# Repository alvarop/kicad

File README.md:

These are some of my KiCAD projects.

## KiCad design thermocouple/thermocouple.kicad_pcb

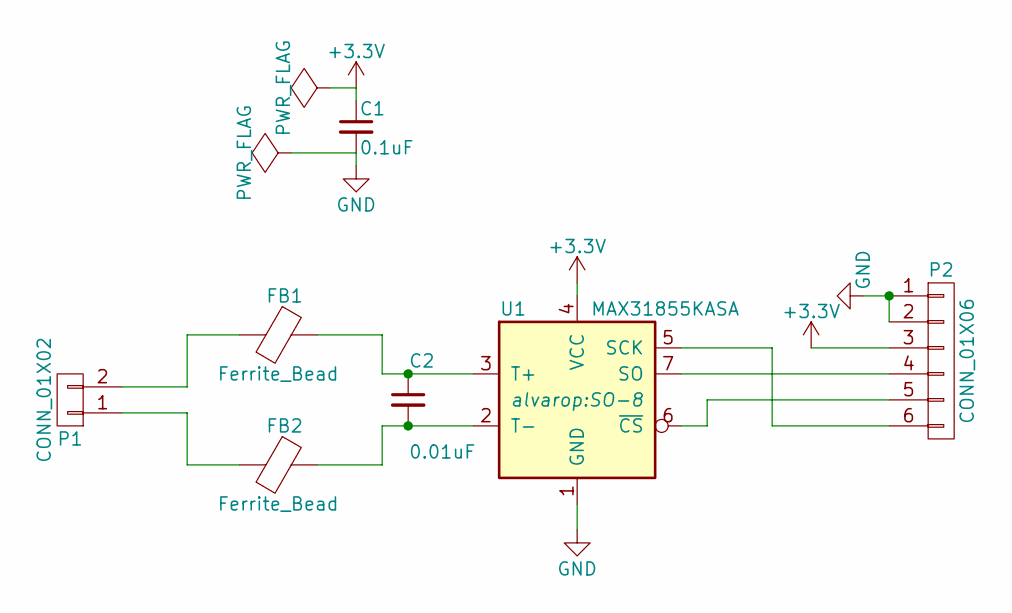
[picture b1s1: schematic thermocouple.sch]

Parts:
C1: 0.1uF; C_0805; MPN CL21B104MBCNNNC
C2: 0.01uF; C_0805; MPN CL21B103KBANNNC
FB1, FB2: Ferrite_Bead; R_0603; MPN BLM18PG471SN1D
P1: CONN_01X02; Pin_Header_Straight_1x02_Pitch2.54mm
P2: CONN_01X06; Pin_Header_Straight_1x06_Pitch2.54mm
U1: MAX31855KASA; SO-8; MPN MAX31855KASA+

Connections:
+3V3: C1.1, P2.3, U1.4 (VCC)
GND: C1.2, P2.1, P2.2, U1.1 (GND)
unnamed: C2.1, FB1.1, U1.3 (T+)
unnamed: C2.2, FB2.1, U1.2 (T-)
unnamed: FB1.2, P1.2
unnamed: FB2.2, P1.1
unnamed: P2.4, U1.7 (SO)
unnamed: P2.5, U1.6 (~CS~)
unnamed: P2.6, U1.5 (SCK)

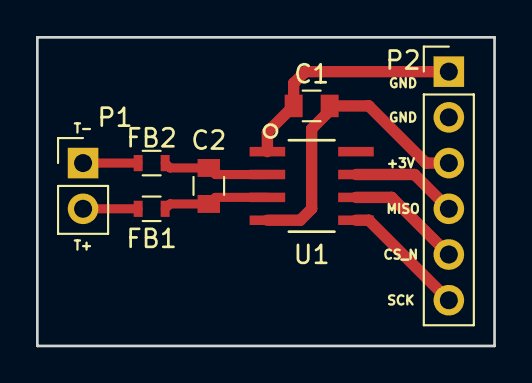
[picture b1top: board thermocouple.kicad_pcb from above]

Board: 2 copper layers, 25.4 x 17.1 mm, 7 parts (0 on the bottom side), 9 nets.

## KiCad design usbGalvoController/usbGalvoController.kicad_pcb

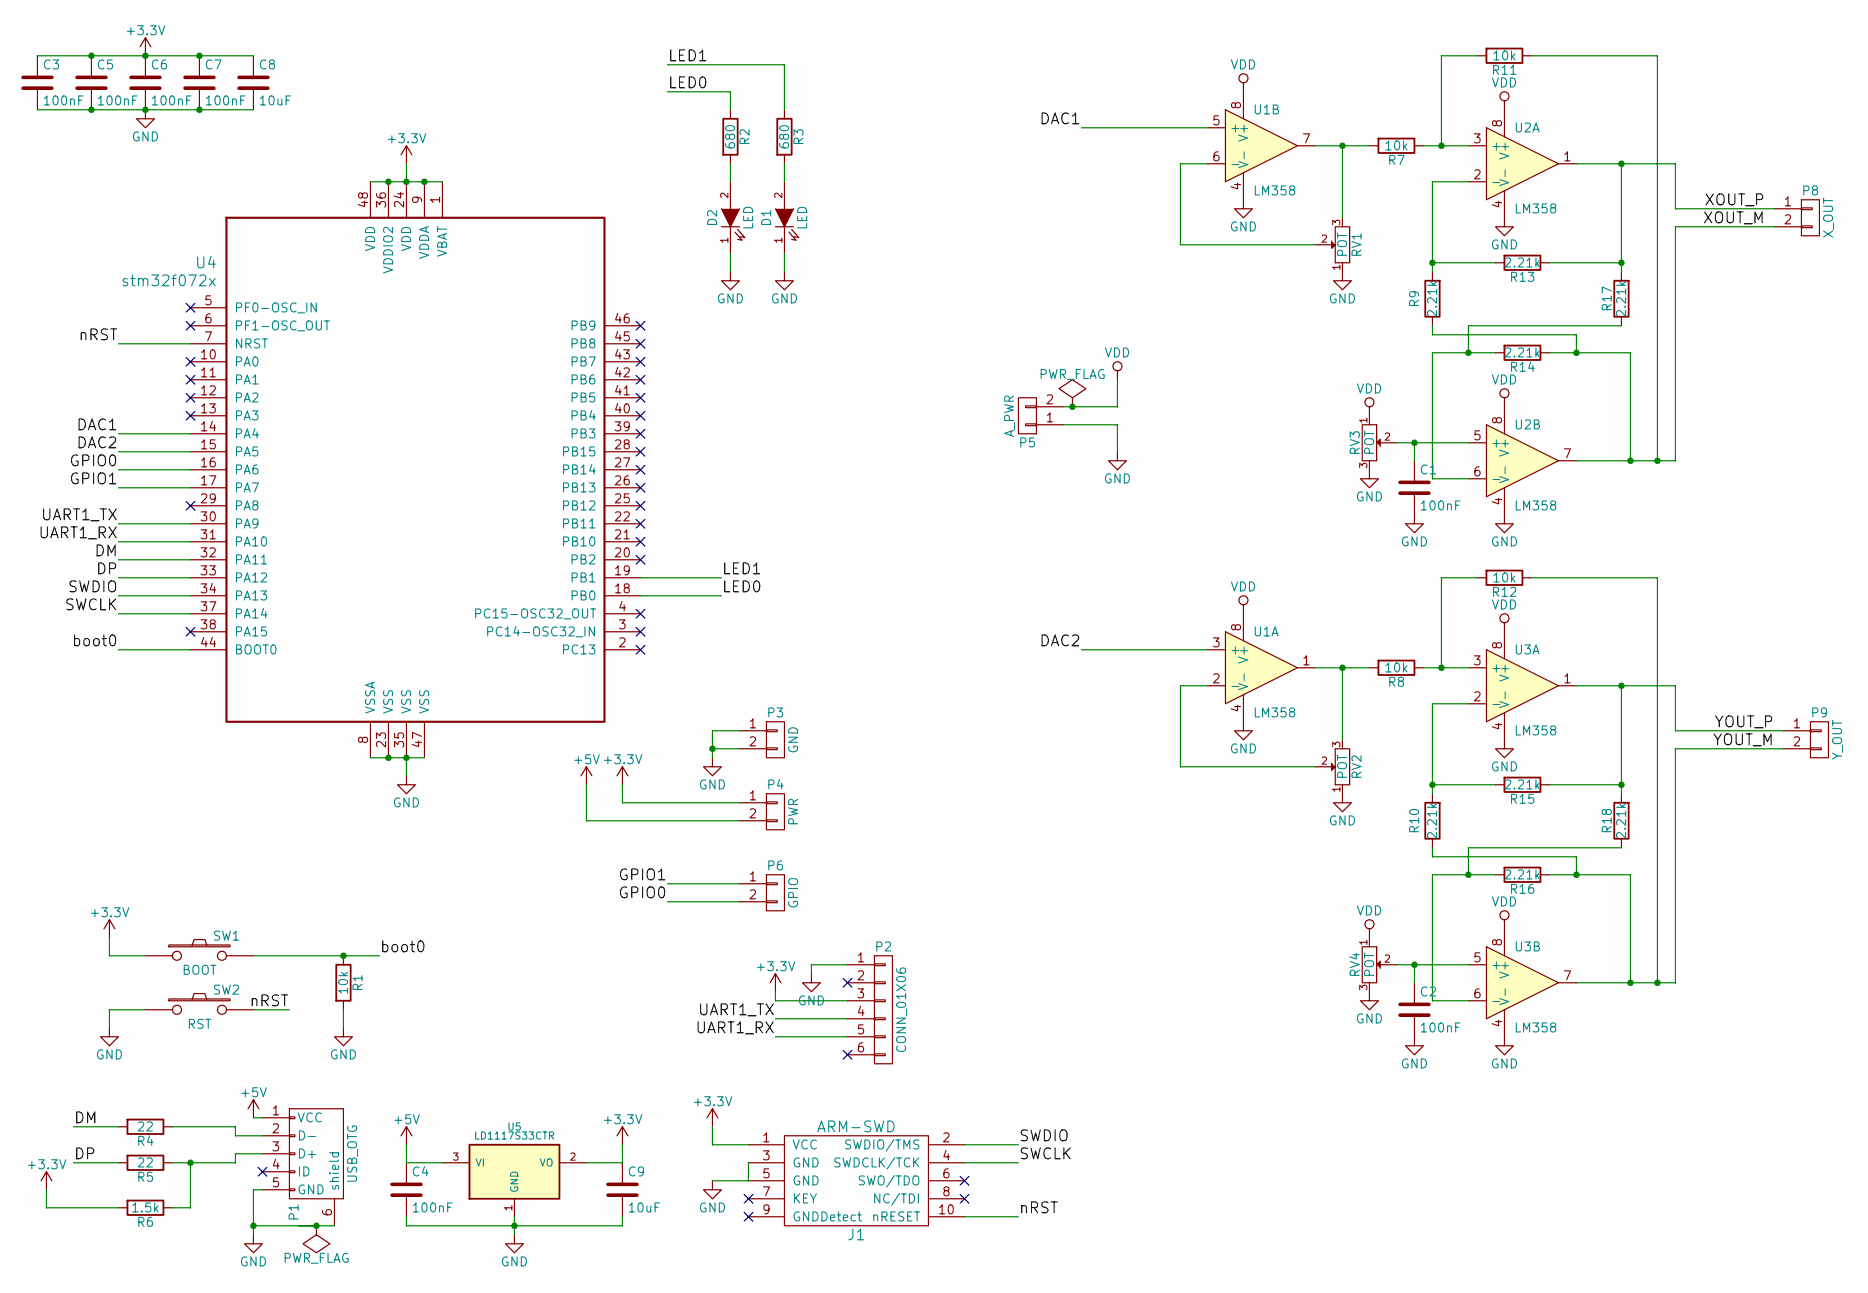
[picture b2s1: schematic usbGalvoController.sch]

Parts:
C1, C2, C3, C4, C5, C6, C7: 100nF; C_0805
C8, C9: 10uF; C_0805
D1, D2: LED; LED_0805
J1: ARM-SWD; ARM_SWD_SMD
P1: USB_OTG; USB_MICRO_B
P2: CONN_01X06; Pin_Header_Straight_1x06
P3: GND; Pin_Header_Straight_1x02
P4: PWR; Pin_Header_Straight_1x02
P5: A_PWR; Pin_Header_Straight_1x02
P6: GPIO; Pin_Header_Straight_1x02
P8: X_OUT; Pin_Header_Straight_1x02
P9: Y_OUT; Pin_Header_Straight_1x02
R1, R7, R8, R11, R12: 10k; R_0805
R2, R3: 680; R_0805
R4, R5: 22; R_0805
R6: 1.5k; R_0805
R9, R10, R13, R14, R15, R16, R17, R18: 2.21k; R_0805
RV1, RV2, RV3, RV4: POT; POT-4mm
SW1: BOOT; PTS645SM43SMTR92
SW2: RST; PTS645SM43SMTR92
U1, U2, U3: LM358; SOIC-8_3.9x4.9mm_Pitch1.27mm
U4: stm32f072x; LQFP48
U5: LD1117S33CTR; SOT-223

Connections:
+3V3: C3.1, C5.1, C6.1, C7.1, C8.1, C9.1, J1.1 (VCC), P2.3, P4.1, R6.2, SW1.1, U4.1 (VBAT), U4.9 (VDDA), U4.24 (VDD), U4.36 (VDDIO2), U4.48 (VDD), U5.2 (VO)
+5V: C4.1, P1.1 (VCC), P4.2, U5.3 (VI)
/DAC1: U1.5 (+), U4.14 (PA4)
/DAC2: U1.3 (+), U4.15 (PA5)
/DM: R4.2, U4.32 (PA11)
/DP: R5.2, U4.33 (PA12)
/GPIO0: P6.2, U4.16 (PA6)
/GPIO1: P6.1, U4.17 (PA7)
/LED0: R2.1, U4.18 (PB0)
/LED1: R3.1, U4.19 (PB1)
/SWCLK: J1.4 (SWDCLK/TCK), U4.37 (PA14)
/SWDIO: J1.2 (SWDIO/TMS), U4.34 (PA13)
/UART1_RX: P2.5, U4.31 (PA10)
/UART1_TX: P2.4, U4.30 (PA9)
/XOUT_M: P8.2, R9.1, R11.1, R14.1, U2.7
/XOUT_P: P8.1, R13.1, R17.2, U2.1
/YOUT_M: P9.2, R10.1, R12.1, R16.1, U3.7
/YOUT_P: P9.1, R15.1, R18.2, U3.1
/boot0: R1.1, SW1.2, U4.44 (BOOT0)
/nRST: J1.10 (nRESET), SW2.2, U4.7 (NRST)
GND: C1.2, C2.2, C3.2, C4.2, C5.2, C6.2, C7.2, C8.2, C9.2, D1.1 (K), D2.1 (K), J1.3 (GND), J1.5 (GND), P1.5 (GND), P1.6 (shield), P2.1, P3.1, P3.2, P5.1, R1.2, RV1.1, RV2.1, RV3.3, RV4.3, SW2.1, U1.4 (V-), U2.4 (V-), U3.4 (V-), U4.8 (VSSA), U4.23 (VSS), U4.35 (VSS), U4.47 (VSS), U5.1 (GND)
unnamed: C1.1, RV3.2, U2.5 (+)
unnamed: C2.1, RV4.2, U3.5 (+)
unnamed: D1.2 (A), R3.2
unnamed: D2.2 (A), R2.2
unnamed: P1.2 (D-), R4.1
unnamed: P1.3 (D+), R5.1, R6.1
unnamed: R7.2, RV1.3, U1.7
unnamed: R8.2, RV2.3, U1.1
unnamed: R10.2, R15.2, U3.2 (-)
unnamed: R7.1, R11.2, U2.3 (+)
unnamed: R8.1, R12.2, U3.3 (+)
unnamed: R9.2, R13.2, U2.2 (-)
unnamed: R14.2, R17.1, U2.6 (-)
unnamed: R16.2, R18.1, U3.6 (-)
unnamed: RV1.2, U1.6 (-)
unnamed: RV2.2, U1.2 (-)
VDD: P5.2, RV3.1, RV4.1, U1.8 (V+), U2.8 (V+), U3.8 (V+)

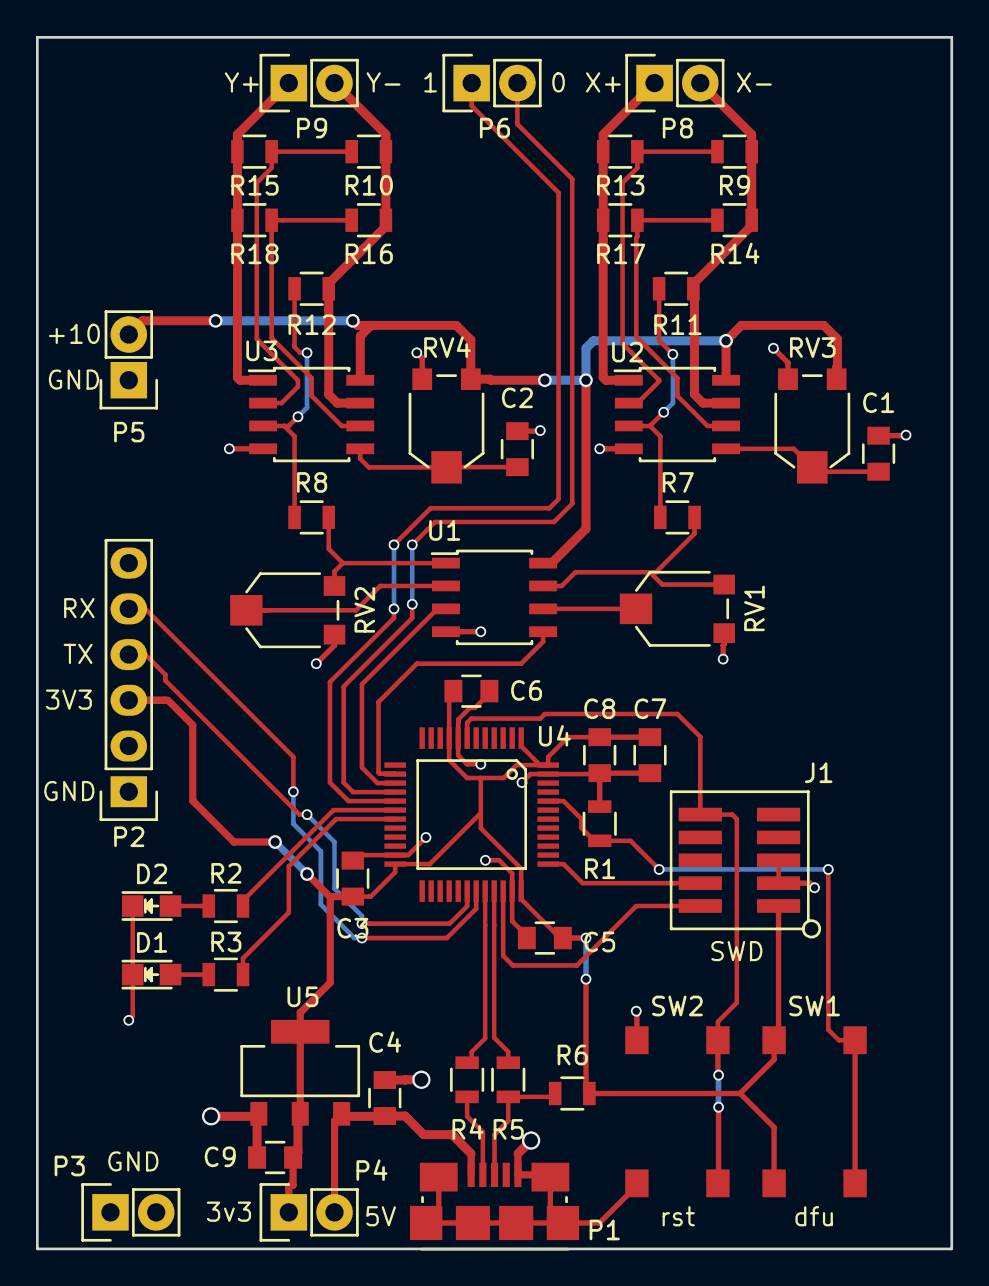
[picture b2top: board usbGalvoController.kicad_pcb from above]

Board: 2 copper layers, 50.8 x 67.3 mm, 49 parts (0 on the bottom side), 38 nets.

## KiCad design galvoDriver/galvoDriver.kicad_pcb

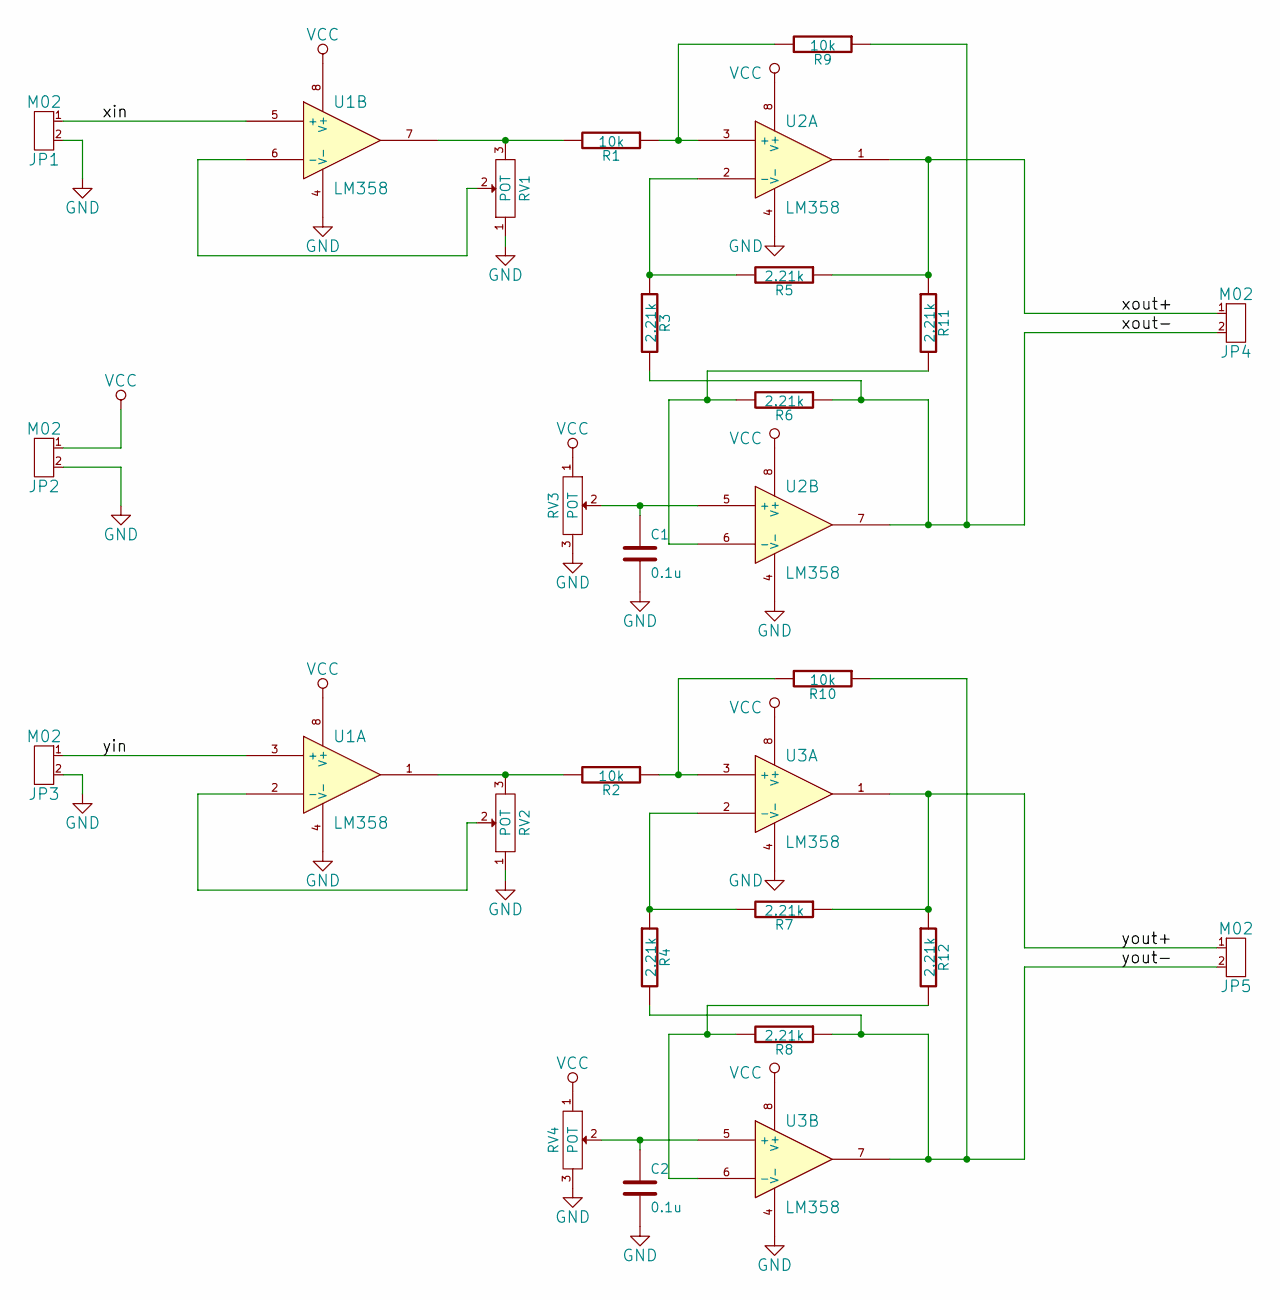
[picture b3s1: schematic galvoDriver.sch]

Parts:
C1, C2: 0.1u; C_0805
JP1, JP2, JP3, JP4, JP5: M02; Pin_Header_Straight_1x02
R1, R2, R9, R10: 10k; R_0805
R3, R4, R5, R6, R7, R8, R11, R12: 2.21k; R_0805
RV1, RV2, RV3, RV4: POT; POT-4mm
U1, U2, U3: LM358; SOIC-8_3.9x4.9mm_Pitch1.27mm

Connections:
/xin: JP1.1, U1.5 (+)
/xout+: JP4.1, R5.1, R11.1, U2.1
/xout-: JP4.2, R3.2, R6.1, R9.1, U2.7
/yin: JP3.1, U1.3 (+)
/yout+: JP5.1, R7.1, R12.1, U3.1
/yout-: JP5.2, R4.2, R8.1, R10.1, U3.7
GND: C1.2, C2.2, JP1.2, JP2.2, JP3.2, RV1.1, RV2.1, RV3.3, RV4.3, U1.4 (V-), U2.4 (V-), U3.4 (V-)
unnamed: C1.1, RV3.2, U2.5 (+)
unnamed: C2.1, RV4.2, U3.5 (+)
unnamed: R1.1, R9.2, U2.3 (+)
unnamed: R1.2, RV1.3, U1.7
unnamed: R2.2, RV2.3, U1.1
unnamed: R3.1, R5.2, U2.2 (-)
unnamed: R4.1, R7.2, U3.2 (-)
unnamed: R2.1, R10.2, U3.3 (+)
unnamed: R6.2, R11.2, U2.6 (-)
unnamed: R8.2, R12.2, U3.6 (-)
unnamed: RV1.2, U1.6 (-)
unnamed: RV2.2, U1.2 (-)
VCC: JP2.1, RV3.1, RV4.1, U1.8 (V+), U2.8 (V+), U3.8 (V+)

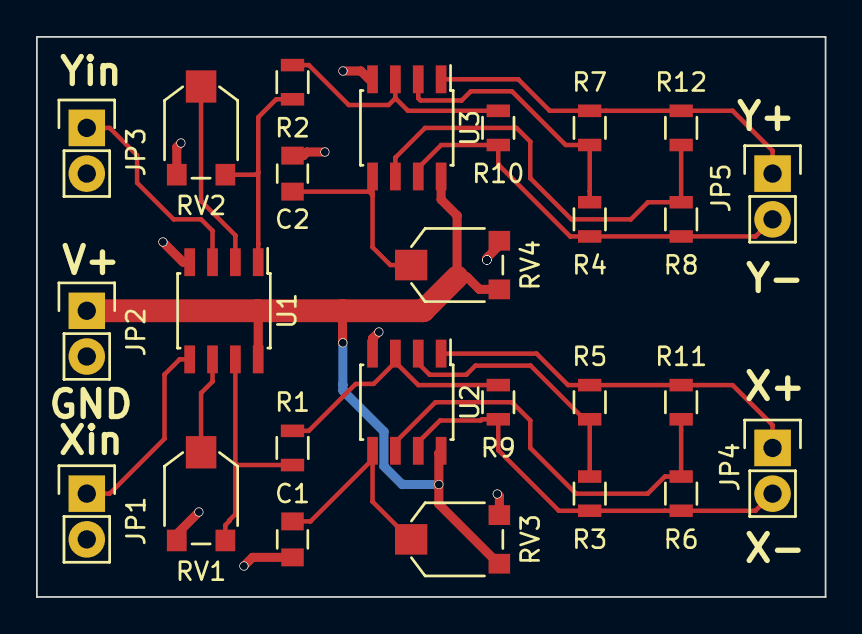
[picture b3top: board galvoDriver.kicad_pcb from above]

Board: 2 copper layers, 43.8 x 31.1 mm, 26 parts (0 on the bottom side), 20 nets.

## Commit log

2015-06-13 adding blank ps4aux project
2015-06-13 Adding usb3a-plug and ps4-aux schematic symbols
2015-06-13 Starting to work on USB3_A_PLUG footprint
2015-06-13 Added pcb edge line for USB3_A_PLUG footprint
2015-06-13 Started PS4_AUX_RECP with SMD pads
2015-06-13 Added shield pins and pcb edge line for PS4_AUX_RECP
2015-06-13 Measured PS4_AUX_RECP with printout and part, seems to be ok-ish now
2015-06-13 Added shield to USB3_A_PLUG and footprint
2015-06-13 Adding ps4aux schematic
2015-06-13 Initial routing of PCB
2015-06-13 Ground fill + shields for PS4AUX
2015-06-13 Make footprints circular since OSHPark doesn't do the oval drills (I don't think at least...)
2015-06-13 re-do board with circular drills
2015-06-13 Ignore all the things!
2015-06-13 This seems important
2015-06-13 Save netlist and ignore more things
2015-06-13 final layout changes
2015-07-12 Moving for nicer directory structure
2015-07-12 Starting to work on galvoDriver
2015-07-12 Op-amp circuit done (I think)
2015-07-12 Adding M02 JP schematic symbol
2015-07-12 Added terminals for galvoDriver
2015-07-12 Whoops, .pretty is the footprint library!
2015-07-12 Adding M02-TH footprint
2015-07-12 Adding murata POT-4mm smt footprint
2015-07-12 Adding oshpark design rules (I think)
2015-07-12 Annotating schematic
2015-07-12 Added footprints
2015-07-12 Adding netlist and initial pcb
2015-07-12 no autosave!
2015-07-12 initial placement
2015-07-12 Flipped amplifiers
2015-07-12 Updated placement
2015-07-12 First pass at layout finished
2015-07-13 Added rear silkscreen
2015-08-26 Adding readme
2015-09-20 Updated version of kicad (replaced old symbols, I think)
2015-09-20 Adding kipart generated library for STM32L151x6
2015-09-20 Started working on usbGalvoController
2015-09-20 Added crystal and USB connections
2015-09-26 Schematic done for usbGalvoController (I think)
2015-09-26 Adding new footprints for USB Micro B, LQFP48, SOT-223, and ATSxxSM crystal oscillator
2015-09-26 Generated netlist
2015-09-26 Layout done! (I think)
2015-09-27 ignore a bunch of things
2015-09-27 Adding BOM for usbGalvoController
2017-01-10 Start updating usbGalvoController schematic
2017-01-11 Finished layout for usbGalvoController v0.2
2017-01-21 Adding part numbers to usbGalvoController
2017-09-30 Adding MDBT42Q
2017-09-30 Import components from Ostur.lib
2017-09-30 Adding footprints from ostur.lib
2017-09-30 Adding RJ11 and MDBT24Q footprints
2017-11-24 Fixed MDBT42Q Footprint
2018-01-01 Adding components and footrprints for Nui project
2018-01-02 Now I know what this dcm file is for...
2018-01-21 Adding NRF52810 library components
2018-05-28 Fixed SHT3x footprint
2018-05-28 Added various components to alvarop.lib
2018-05-28 Adding various footprints
2018-05-28 Adding old thermocouple project
2018-05-28 Remove paste layer for TC2030-NL footprint
2018-12-23 Adding various new footprints/symbols
2018-12-23 pads were swapped
2018-12-23 reduced pad size
2019-01-26 Adding custom Kicad BOM Wizard template
    https://www.hashdefineelectronics.com/kicad-bom-wizard/
2019-01-26 Fixed bmp280 silkscreen
2019-01-26 Adding various components/footprints
2019-05-21 Adding NRF82811
2019-05-22 Fix pin types
2019-06-20 Adding chaac-radio symbol
2019-06-20 Added 3d model for s2b-ph-sm4-tb
2019-06-20 Adding a bunch of new parts and 3d models!
2019-09-22 Modified MCP73871 to have slightly thinner pads to allow 4 mil soldermask webbing between them
2019-09-22 Forgot to add all these components...
2019-12-11 Adding some parts to lib
2019-12-11 Adding several footprints and 3d files
2020-03-20 Adding kicad bom template
2020-03-20 Adding script that re-formats kicad bom (from template) for PB io
    Example:
    python3 ./pb_csv.py ../../usb_c_power/usb_c_power_BOM.csv ../../usb_c_power/usb_c_power_BOM_PBIO.csv
2020-03-20 Updating lib
2020-03-23 Adding paste-in-hole for molex usb-c connector
2020-03-23 Adding new components and models
2020-04-18 lib update
2020-06-05 Fixed TE_1825910-6 footprint and added E22-X00M22S footprint/symbol
2020-06-16 Fixed pinout for MOLEX-0480371000
2020-06-16 Added symbol for TPS7A0530PDBVT
2020-06-16 Added NRF QFN48 footprint with vias
2020-11-15 Adding a bunch of new parts
2021-05-28 adding new stuff
2021-10-02 DKPN fix
2021-10-02 add old parts
